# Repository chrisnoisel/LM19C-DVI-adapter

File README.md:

# LM19C-TMDS-adapter
The LM19C is a 19" flat screen. It is old but I still use it.
It has VGA and TMDS (DVI/HDMI) inputs but the later uses a male VGA socket so I looked at the pcb and the pinout should be the following :

1. DDC Clock
2. GND
3. TMDS RX2P
4. TMDS RX1P
5. GND
6. DDC Data
7. TMDS RX2N
8. TMDS RX1N
9. HotPlug
10. +5v standby
11. RX0P
12. RX0N
13. GND
14. RXCP
15. RXCN

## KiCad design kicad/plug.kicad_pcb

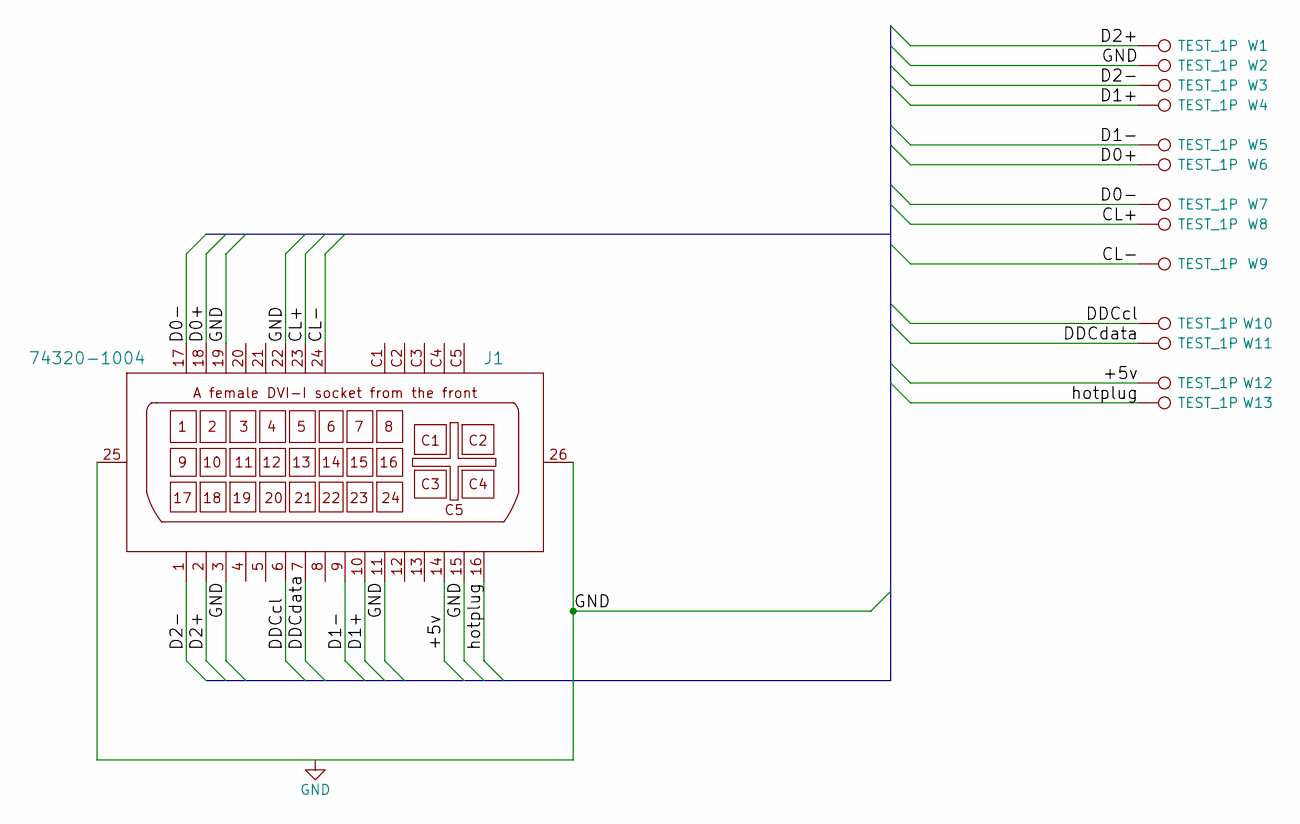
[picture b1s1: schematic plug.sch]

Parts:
J1: 74320-1004; DVI-RECEPT-RA-HDMI
W1, W2, W3, W4, W5, W6, W7, W8, W9, W10, W11, W12, W13: TEST_1P; pad

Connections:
/+5v: J1.14 (+5V), W12.1
/CL+: J1.23 (TMDS_clock+), W8.1
/CL-: J1.24 (TMDS_clock-), W9.1
/D0+: J1.18 (TMDS_data_0+), W6.1
/D0-: J1.17 (TMDS_data_0-), W7.1
/D1+: J1.10 (TMDS_Data_1+), W4.1
/D1-: J1.9 (TMDS_Data_1-), W5.1
/D2+: J1.2 (TMDS_Data_2+), W1.1
/D2-: J1.1 (TMDS_Data_2-), W3.1
/DDCcl: J1.6 (DDC_clock), W10.1
/DDCdata: J1.7 (DDC_data), W11.1
/hotplug: J1.16 (Hot_plug_detect), W13.1
GND: J1.3 (TMDS_Data_2/4_shield), J1.11 (TMDS_Data_1/3_shield), J1.15 (Ground), J1.19 (TMDS_data_0/5_shield), J1.22 (TMDS_clock_shield), J1.25 (SHIELD), J1.26 (SHIELD), W2.1

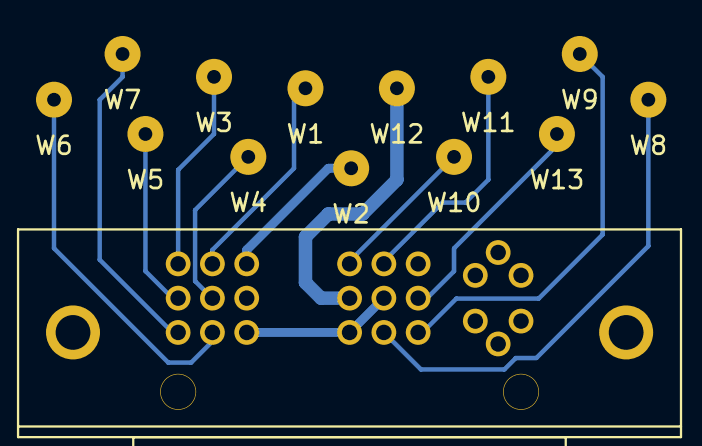
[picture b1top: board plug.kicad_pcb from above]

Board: 2 copper layers, 14 parts (0 on the bottom side), 13 nets.

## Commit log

2015-12-08 added hdmi and dvi on schematic
2016-01-03 added pinout info
2016-01-03 fixed dodgy markdown
2016-01-03 changed HDMI socket for SMD footprint + rewiring + all shields connected to ground
2016-01-03 reduced pcb height
2016-01-05 renamed project to include HDMI feature
2016-12-17 updated gitignore
2016-12-17 simplier version since hdmi is a pain to manage.
2016-12-18 added pad footprint
2016-12-24 pads layout suits cable connexion better
